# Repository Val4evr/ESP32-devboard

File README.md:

# ESP32-devboard

I made this ESP-32 Development board to learn KiCad. It is heavilly based on the [ESP32-DevKit C](https://www.espressif.com/en/products/devkits/esp32-devkitc/resources) reference implementation, but with the redundant micro USB port replaced with USB-C. Here's a ray-traced KiCad render:

# Usage
This repo comes with the footprints, 3D models and everything needed to reproduce the renders. Also, this KiCad project uses the [KiKit](https://github.com/yaqwsx/KiKit) extension to create the below panelization in a format compatible with the [JLCPCB PCBA service](https://jlcpcb.com/smt-assembly). 

The resultant production files are [here](https://github.com/Val4evr/ESP32-devboard/blob/main/ESP32_panelized_outputgerbers.zip). If you want to edit the design you will have to re-create the panel and gerbers for production:
1. [Setup KiKit](https://yaqwsx.github.io/KiKit/latest/installation/intro/)
2. Open an empty KiCad pcbnew instance
3. Click on the KiKit icon to open the GUI.
4. Select the updated pcb design and output directory (I used `/panelized`) 
5. Import my KiKit [JSON config](https://github.com/Val4evr/ESP32-devboard/blob/main/panelized/kikit_config.json)
6. Panelize!

If you then decide it's good enough for production, run the following snippet to get the gerbers, specifying the path to the panel. 
```
kikit fab jlcpcb --nametemplate "ESP32_panelized_output{}" --no-drc --assembly --schematic <path to schematic file> <path to PCB file> <path to output directory>
```

This will produce gerber, drill and position files for JLC PCB. 

# Previous revisions:
The PCB did not work on first try because of two misconfigured 0ohm DNP resistors on the USB serial traces. As a result I had to solder two strands of solder wick directly to the serial converter chip and ESP32, and hold them in place with copious quantities of tape.

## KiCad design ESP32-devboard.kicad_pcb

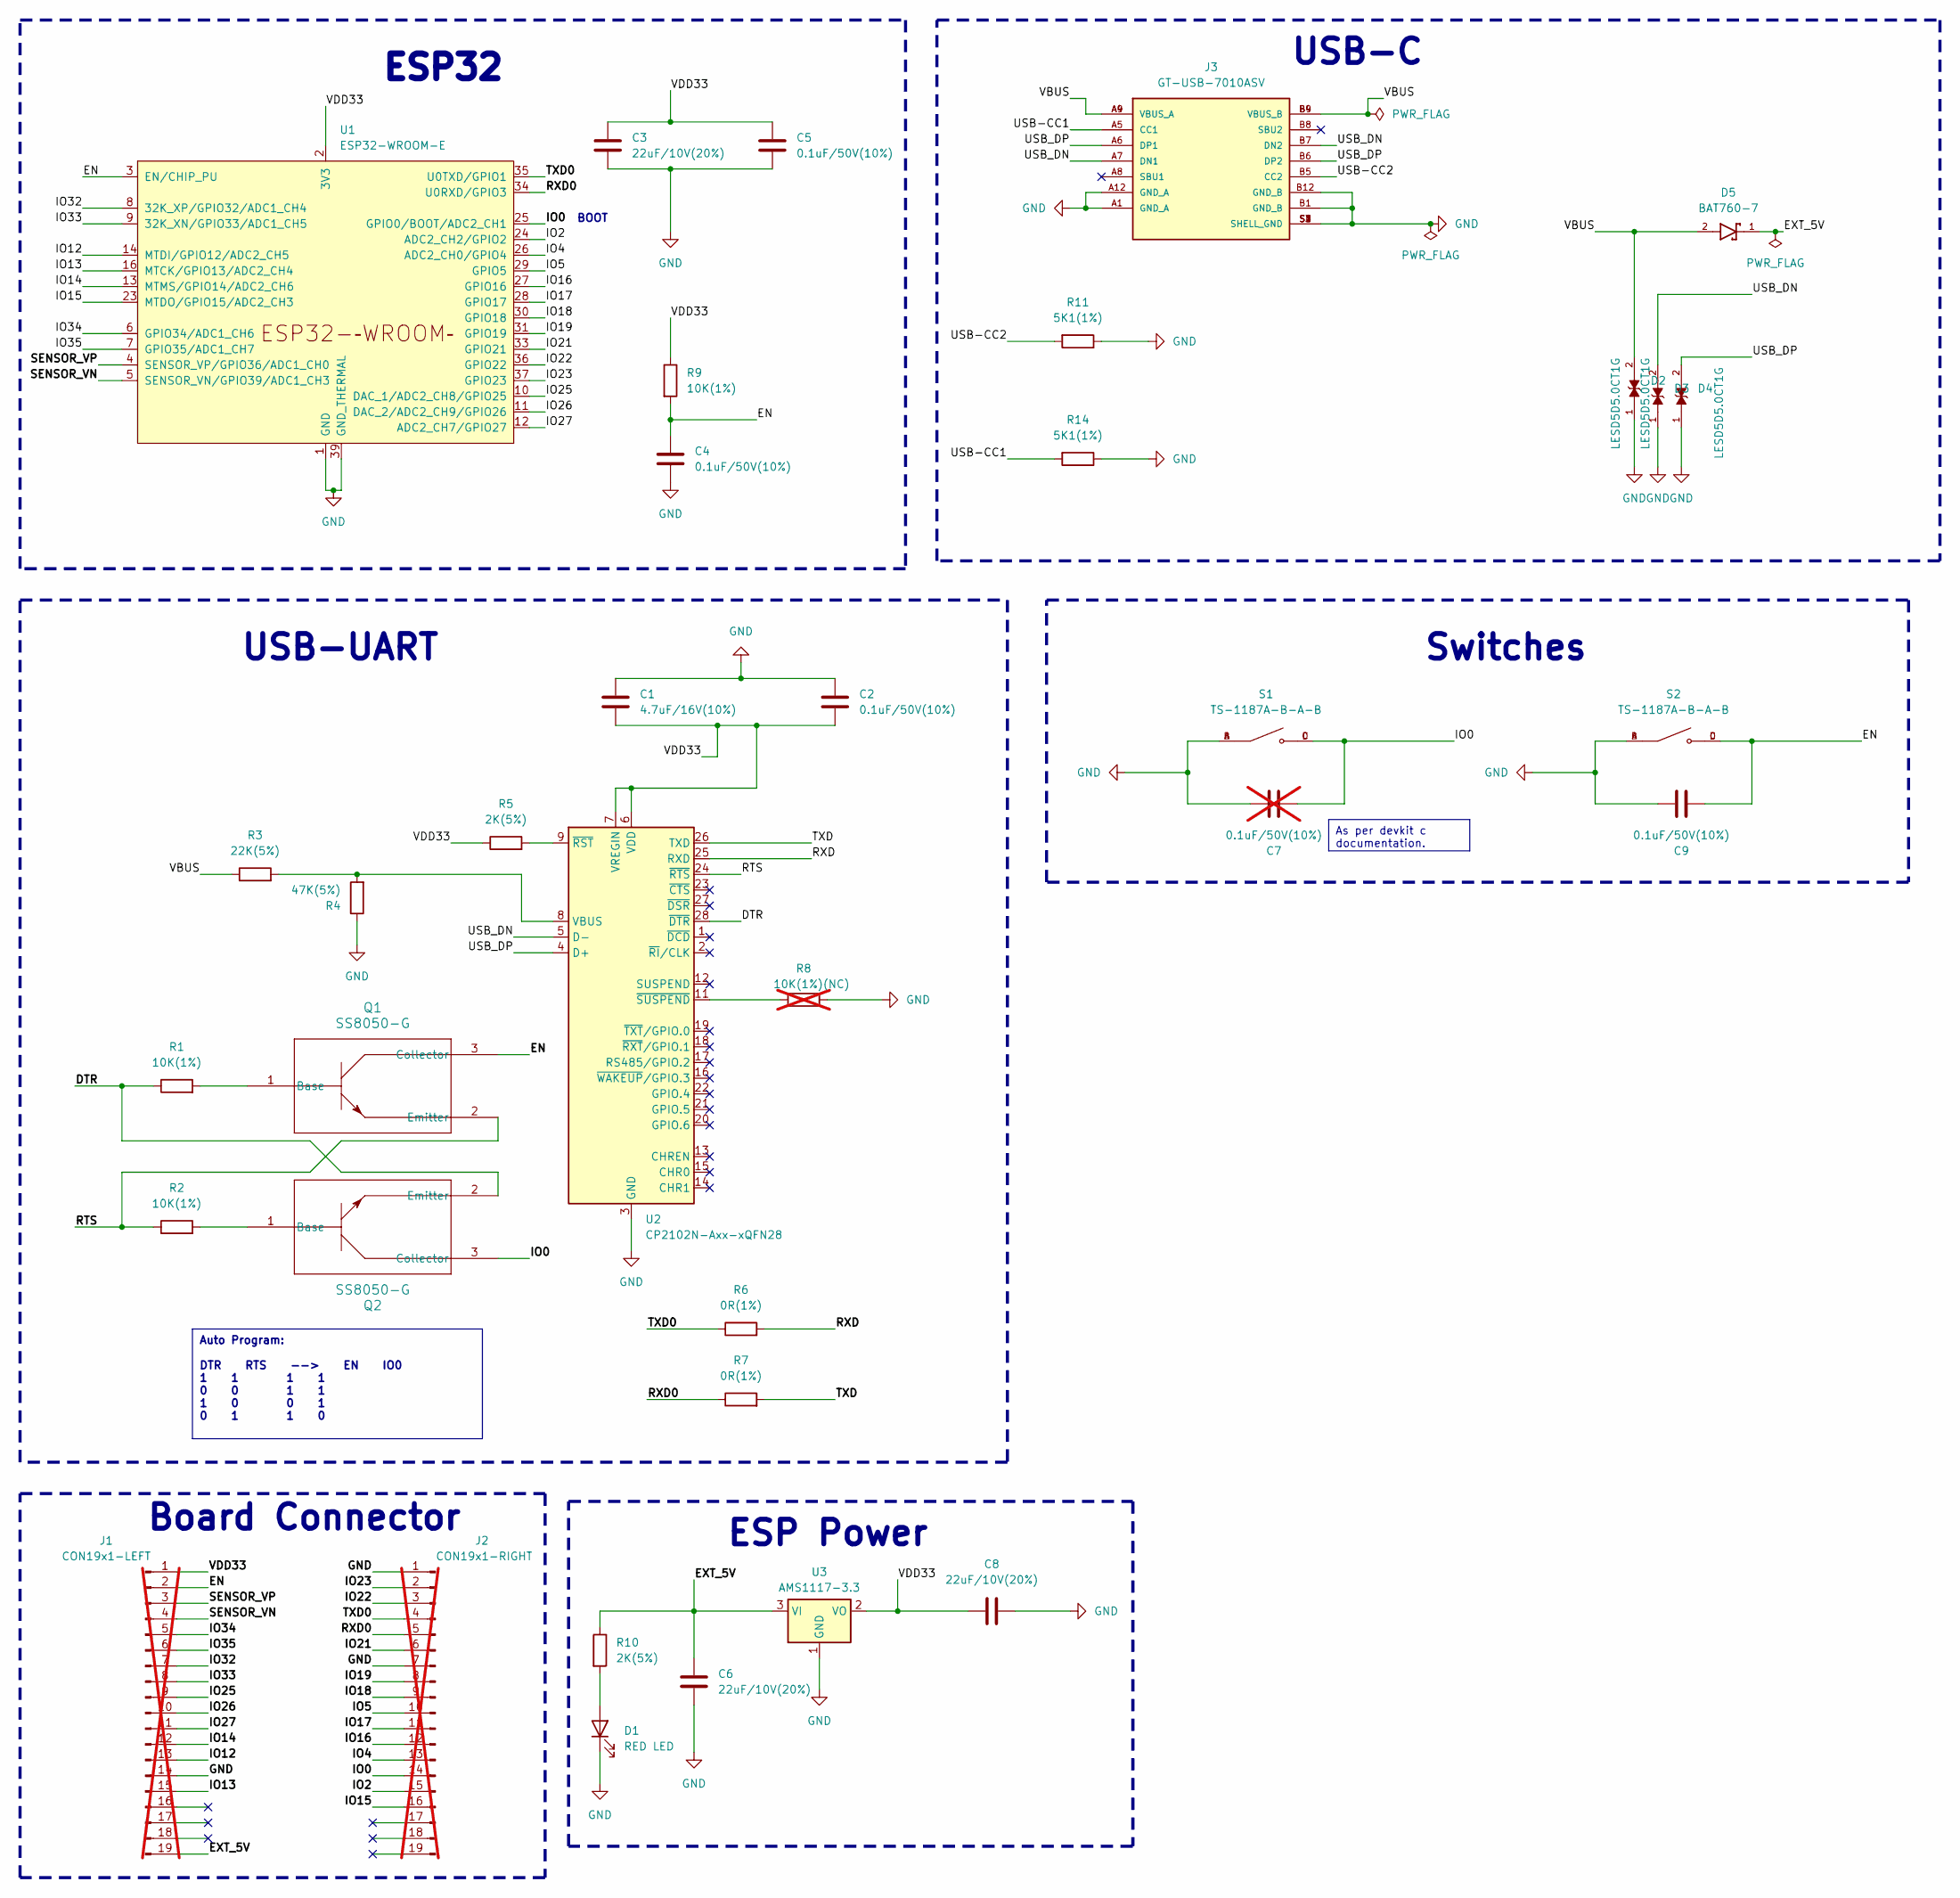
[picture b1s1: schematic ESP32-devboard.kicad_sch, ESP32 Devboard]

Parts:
C1: 4.7uF/16V(10%); C_0603_1608Metric; LCSC C19666
C2, C4, C5, C9: 0.1uF/50V(10%); C_0402_1005Metric; LCSC C307331
C3, C6, C8: 22uF/10V(20%); C_0805_2012Metric; LCSC C45783
C7: 0.1uF/50V(10%); C_0402_1005Metric; LCSC C307331; not fitted
D1: RED LED; D_0603_1608Metric; LCSC C2286
D2, D3, D4: LESD5D5.0CT1G; D_SOD-523; LCSC C383211
D5: BAT760-7; D_SOD-323; LCSC C124187
J1: CON19x1-LEFT; PinSocket_1x19_P2.54mm_Vertical; not fitted
J2: CON19x1-RIGHT; PinSocket_1x19_P2.54mm_Vertical; not fitted
J3: GT-USB-7010ASV; GT-USB-7010; LCSC C2988369
Q1, Q2: SS8050-G; TSOT-23; LCSC C164885
R1, R2, R9: 10K(1%); C_0603_1608Metric; LCSC C25804
R3: 22K(5%); C_0805_2012Metric; LCSC C17560
R4: 47K(5%); C_0603_1608Metric; LCSC C25819
R5, R10: 2K(5%); C_0603_1608Metric; LCSC C22975
R6, R7: 0R(1%); C_0402_1005Metric; LCSC C17168
R8: 10K(1%)(NC); C_0603_1608Metric; LCSC C25804; not fitted
R11, R14: 5K1(1%); R_0402_1005Metric; LCSC C25905
S1, S2: TS-1187A-B-A-B; SW_TS-1187A-B-A-B; PARTREV A0; LCSC C318884
U1: ESP32-WROOM-E; ESP32-WROOM-32E; LCSC C701341
U2: CP2102N-Axx-xQFN28; QFN-28-1EP_5x5mm_P0.5mm_EP3.35x3.35mm; LCSC C964632
U3: AMS1117-3.3; SOT-223-3_TabPin2; LCSC C6186

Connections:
/DTR: Q2.2 (Emitter), R1.1, U2.28 (~DTR)
/EN: C4.1, C9.1, J1.2, Q1.3 (Collector), R9.2, S2.C, S2.D, U1.3 (EN/CHIP_PU)
/EXT_5V: C6.1, D5.1, J1.19, R10.1, U3.3 (VI)
/IO0: C7.1, J2.14, Q2.3 (Collector), S1.C, S1.D, U1.25 (GPIO0/BOOT/ADC2_CH1)
/IO2: J2.15, U1.24 (ADC2_CH2/GPIO2)
/IO4: J2.13, U1.26 (ADC2_CH0/GPIO4)
/IO5: J2.10, U1.29 (GPIO5)
/IO12: J1.13, U1.14 (MTDI/GPIO12/ADC2_CH5)
/IO13: J1.15, U1.16 (MTCK/GPIO13/ADC2_CH4)
/IO14: J1.12, U1.13 (MTMS/GPIO14/ADC2_CH6)
/IO15: J2.16, U1.23 (MTDO/GPIO15/ADC2_CH3)
/IO16: J2.12, U1.27 (GPIO16)
/IO17: J2.11, U1.28 (GPIO17)
/IO18: J2.9, U1.30 (GPIO18)
/IO19: J2.8, U1.31 (GPIO19)
/IO21: J2.6, U1.33 (GPIO21)
/IO22: J2.3, U1.36 (GPIO22)
/IO23: J2.2, U1.37 (GPIO23)
/IO25: J1.9, U1.10 (DAC_1/ADC2_CH8/GPIO25)
/IO26: J1.10, U1.11 (DAC_2/ADC2_CH9/GPIO26)
/IO27: J1.11, U1.12 (ADC2_CH7/GPIO27)
/IO32: J1.7, U1.8 (32K_XP/GPIO32/ADC1_CH4)
/IO33: J1.8, U1.9 (32K_XN/GPIO33/ADC1_CH5)
/IO34: J1.5, U1.6 (GPIO34/ADC1_CH6)
/IO35: J1.6, U1.7 (GPIO35/ADC1_CH7)
/RTS: Q1.2 (Emitter), R2.1, U2.24 (~RTS)
/RXD: R6.2, U2.25 (RXD)
/RXD0: J2.5, R7.1, U1.34 (U0RXD/GPIO3)
/SENSOR_VN: J1.4, U1.5 (SENSOR_VN/GPIO39/ADC1_CH3)
/SENSOR_VP: J1.3, U1.4 (SENSOR_VP/GPIO36/ADC1_CH0)
/TXD: R7.2, U2.26 (TXD)
/TXD0: J2.4, R6.1, U1.35 (U0TXD/GPIO1)
/USB-CC1: J3.A5 (CC1), R14.2
/USB-CC2: J3.B5 (CC2), R11.2
/USB_DN: D3.2, J3.A7 (DN1), J3.B7 (DN2), U2.5 (D-)
/USB_DP: D4.2, J3.A6 (DP1), J3.B6 (DP2), U2.4 (D+)
/VBUS: D2.2, D5.2, J3.A4 (VBUS_A), J3.A9 (VBUS_A), J3.B4 (VBUS_B), J3.B9 (VBUS_B), R3.1
/VDD33: C1.2, C2.2, C3.1, C5.1, C8.1, J1.1, R5.1, R9.1, U1.2 (3V3), U2.6 (VDD), U2.7 (VREGIN), U3.2 (VO)
GND: C1.1, C2.1, C3.2, C4.2, C5.2, C6.2, C7.2, C8.2, C9.2, D1.1 (K), D2.1, D3.1, D4.1, J1.14, J2.1, J2.7, J3.A1 (GND_A), J3.A12 (GND_A), J3.B1 (GND_B), J3.B12 (GND_B), J3.S1 (SHELL_GND), J3.S2 (SHELL_GND), J3.S3 (SHELL_GND), J3.S4 (SHELL_GND), R4.1, R8.2, R11.1, R14.1, S1.A, S1.B, S2.A, S2.B, U1.1 (GND), U1.15 (GND), U1.38 (GND), U1.39 (GND_THERMAL), U2.3 (GND), U2.29 (GND), U3.1 (GND)
unnamed: D1.2 (A), R10.2
unnamed: Q1.1 (Base), R1.2
unnamed: Q2.1 (Base), R2.2
unnamed: R3.2, R4.2, U2.8 (VBUS)
unnamed: R5.2, U2.9 (~RST)
unnamed: R8.1, U2.11 (~SUSPEND)

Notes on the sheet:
Auto Program: DTR RTS --> EN IO0 1 1 1 1 0 0 1 1 1 0 0 1 0 1 1 0
As per devkit c documentation.
ESP Power
Board Connector
Switches
USB-C
ESP32
BOOT
USB-UART

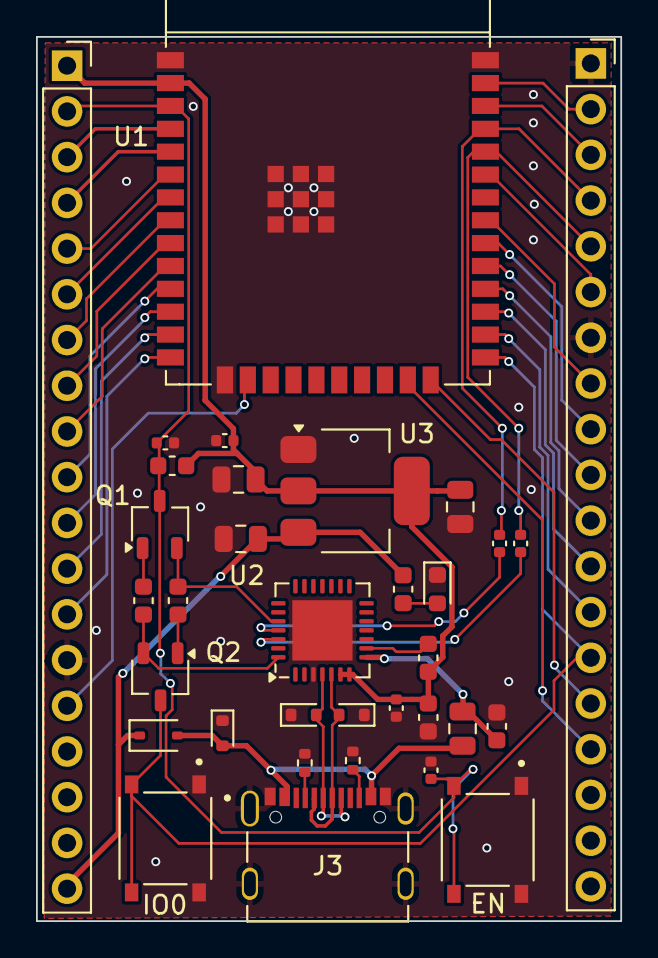
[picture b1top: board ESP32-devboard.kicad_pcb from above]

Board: 2 copper layers, 32.5 x 49.1 mm, 34 parts (0 on the bottom side), 44 nets.

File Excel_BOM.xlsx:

Simple Components:
Type | Comment / Value | Designator | Footprint / Package | JLCPCB Part# | Library Type (Ex/Exp/Bc) | Notes:
Capacitor | 4.7uF/16v(10%) | C1 | 0603 | C19666 | Basic
Capacitor | 0.1uF/50V(10%) | C2, C4, C5, C7, C9 | 0402 | C307331 | Basic
Capacitor | 22uF/10V(20%) | C3, C6, C8 | 0805 | C45783 | Basic
Resistor | 10K(5%) | R1, R2 | 1206 | C17902 | Basic
Resistor | 22K(5%) | R3 | 0805 | C17560 | Basic | Changed from 22.1K
Resistor | 47K(5%) | R4 | 0603 | C25819 | Basic | Changed from 44.5K.
Resistor | 2K(5%) | R5, R10 | 0603 | C22975 | Basic
Resistor | 0R (5%) | R6, R7 | 0402 | C17168 | Basic | 0 ohm resistor. Verify is required.
Resistor | 10K(1%) | R8, R9, R11, R12, R13, R14 | 0603 | C25804 | Basic | R8 is marked as NC. Verify.
Transistor | SS8050-G | Q1, Q2 | SOT23 | C164885 | External
ESD Protection | LESD5D5.OCT1G | D2, D3, D4 | SOD-523 | C383211 | External
Diode | BAT760-7 | D5 | SOD-323 | C124187 | External
LED | RED LED | D1 | 0603 | C2286 | Basic
Voltage Regulator | AMS1117-3.3 | U3 | SOT-223-3 | C6186 | Basic
Switch | TS-1187A-B-A-B | SW1, SW2 | SMD | C318884 | External
Complex Components:
Type | Comment / Value | Designator | Footprint / Package | JLCPCB Part# | Library Type (Ex/Exp/Bc) | Notes: | e
USB-C | 16Pin USB-C Connector | J3 | SMD | C2988369 | External
ESP32 | ESP32-WROOM-32E-N4 | U1 | SMD,18x25.5mm | C701341 | External
USB-UART | CP2102N-A02 | U2 | QFN-28-EP(5x5) | C964632 | External

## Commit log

2024-06-07 Create LICENSE
2025-02-06 Add project files
2025-02-06 Remove command.md and update README
2025-02-06 Removed unused images.
